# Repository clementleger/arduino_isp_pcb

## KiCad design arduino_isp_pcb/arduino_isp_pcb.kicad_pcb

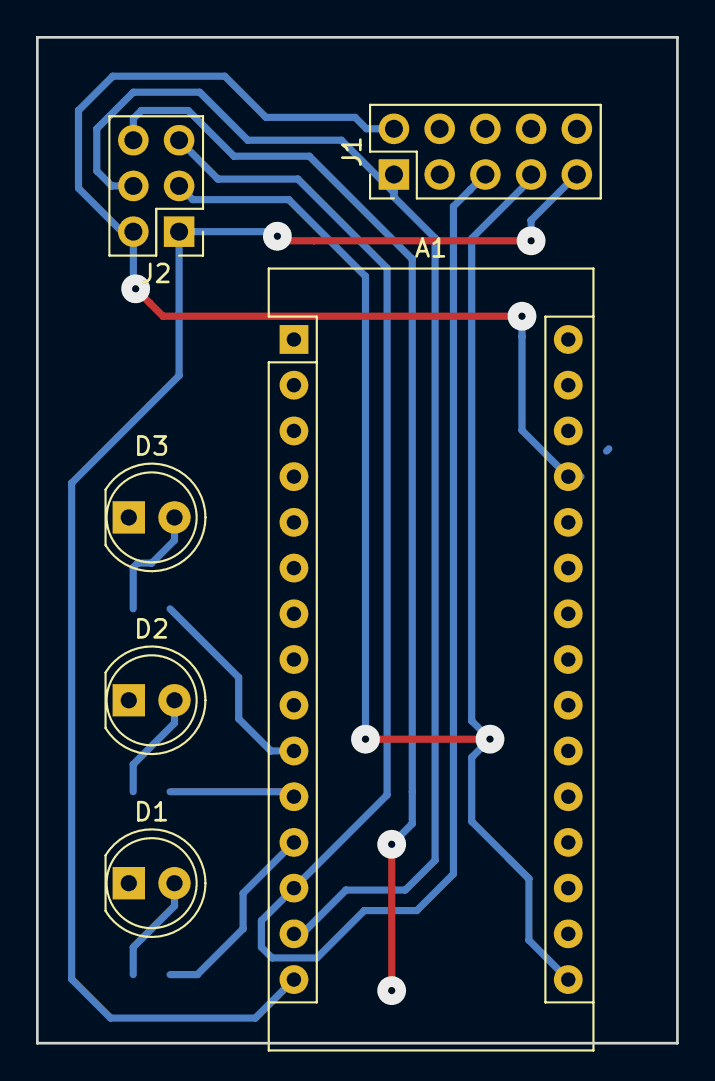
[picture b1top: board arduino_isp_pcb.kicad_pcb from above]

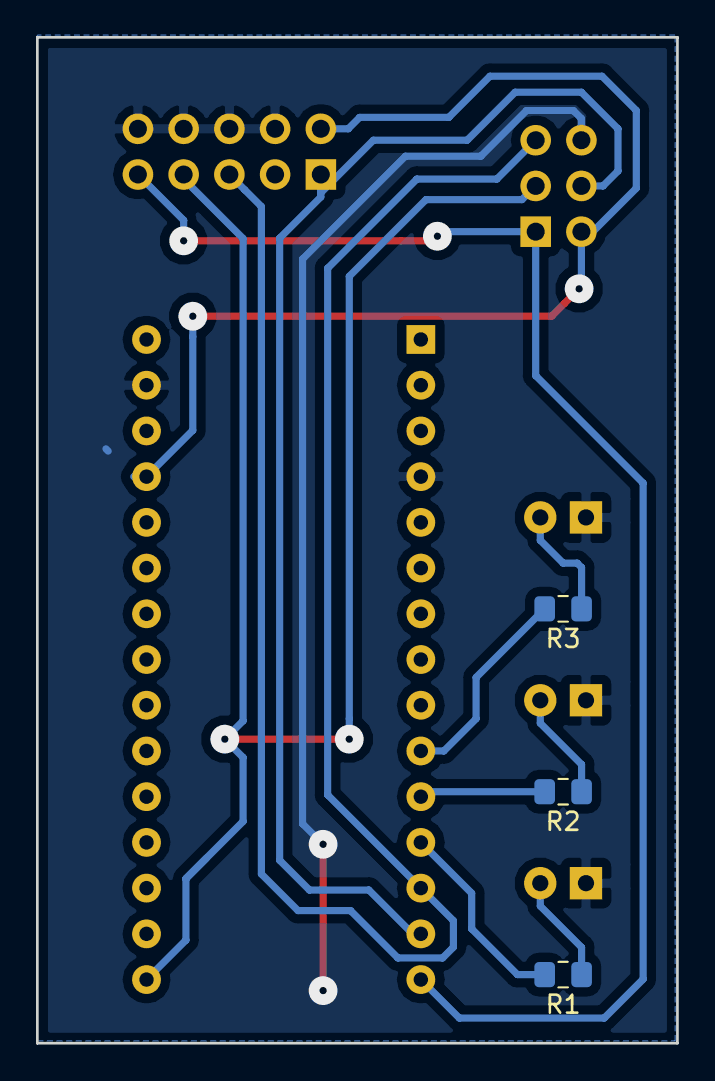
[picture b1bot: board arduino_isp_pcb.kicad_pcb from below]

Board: 2 copper layers, 35.6 x 55.9 mm, 9 parts (3 on the bottom side), 12 nets.

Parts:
A1: Arduino_Nano_v3.x; Arduino_Nano
D1, D2, D3: LED; LED_D5.0mm
J1: Conn_02x05_Odd_Even; PinHeader_2x05_P2.54mm_Vertical
J2: Conn_02x03_Odd_Even; PinHeader_2x03_P2.54mm_Vertical
R1, R2, R3: R; R_0805_2012Metric_Pad1.15x1.40mm_HandSolder

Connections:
+5V: A1.27, J1.2, J2.2
GND: A1.4, A1.29, D1.1, D2.1, D3.1, J1.4, J1.6, J1.8, J1.10, J2.6
LED_ERROR: A1.11, R2.2
LED_HB: A1.12, R1.2
LED_PROG: A1.10, R3.2
MISO: A1.15, J1.9, J2.1
MOSI: A1.14, J1.1, J2.4
unnamed: D1.2, R1.1
unnamed: D2.2, R2.1
unnamed: D3.2, R3.1
SCLK: A1.16, J1.7, J2.3
T_RST: A1.13, J1.5, J2.5

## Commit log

2018-07-29 PCB: add initial files
    Add schematic only
2018-07-29 PCB: add pcb
    Route PCB
2018-07-30 PCB: add 6 pins AVR ISP connector
